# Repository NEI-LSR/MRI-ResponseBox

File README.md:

# MRI-ResponseBox
 Fiber optic manual response system for MRI use
 
 Contains:
  - **Code** contains the code loaded on the [Arduino](https://www.arduino.cc/en/Guide/Environment)
  - **FreeCad** contains the 3D model of the box using [FreeCad](https://www.freecadweb.org/)
  - **Eagle** contains the schematic of the electronics (see software [here](https://www.autodesk.com/products/eagle/features))

Note that the box should be put outside the scanner room (only the optic fiber should enter the room).

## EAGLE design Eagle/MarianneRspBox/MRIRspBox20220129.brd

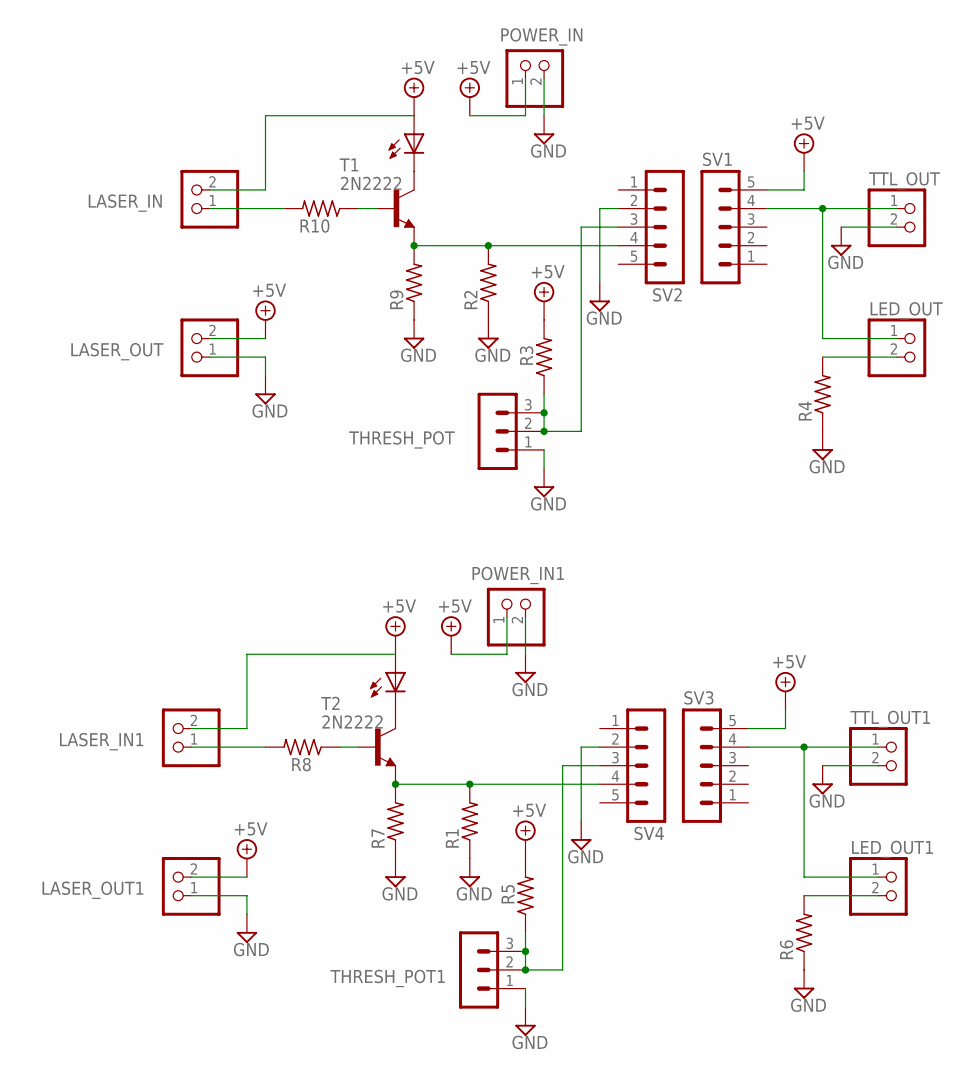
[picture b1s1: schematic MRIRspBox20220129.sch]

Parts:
LASER_IN, LASER_IN1: PINHD-1X2; 1X02
LASER_OUT, LASER_OUT1: PINHD-1X2; 1X02
LED1, LED2: LED_ELD260; LED_LD260
LED_OUT, LED_OUT1: PINHD-1X2; 1X02
POWER_IN, POWER_IN1: PINHD-1X2; 1X02
R1, R2, R3, R4, R5, R6, R7, R8, R9, R10: R-US_0207/12; 0207/12
SV1, SV2, SV3, SV4: MA05-1
T1, T2: 2N2222; TO92-EBC-OVAL
THRESH_POT, THRESH_POT1: MA03-1
TTL_OUT, TTL_OUT1: PINHD-1X2; 1X02

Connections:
+5V: LASER_IN.2, LASER_IN1.2, LASER_OUT.2, LASER_OUT1.2, LED1.A, LED2.A, POWER_IN.1, POWER_IN1.1, R3.2, R5.2, SV1.5, SV3.5
GND: LASER_OUT.1, LASER_OUT1.1, POWER_IN.2, POWER_IN1.2, R1.1, R2.1, R4.1, R6.1, R7.1, R9.1, SV2.2, SV4.2, THRESH_POT.1, THRESH_POT1.1, TTL_OUT.2, TTL_OUT1.2
unnamed: LED_OUT1.1, SV3.4, TTL_OUT1.1
unnamed: R5.1, SV4.3, THRESH_POT1.2, THRESH_POT1.3
unnamed: LED_OUT.1, SV1.4, TTL_OUT.1
unnamed: R3.1, SV2.3, THRESH_POT.2, THRESH_POT.3
unnamed: LED_OUT1.2, R6.2
unnamed: LASER_IN1.1, R8.2
unnamed: LED_OUT.2, R4.2
unnamed: R8.1, T2.B
unnamed: LED2.K (C), T2.C
unnamed: R1.2, R7.2, SV4.4, T2.E
unnamed: LASER_IN.1, R10.2
unnamed: R10.1, T1.B
unnamed: LED1.K (C), T1.C
unnamed: R2.2, R9.2, SV2.4, T1.E

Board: 2 copper layers, 30 parts (0 on the bottom side), 16 nets, no tracks yet.

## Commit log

2022-04-20 Initial import
